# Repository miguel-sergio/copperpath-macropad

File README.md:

# RP2040 Macropad

A 9-key macropad with a rotary encoder and RGB lighting under every key, built around the RP2040.

I made it as an open project, so anyone can learn from it, change it or build one. The repo has the full KiCad project, the files to order it assembled at JLCPCB, and the notes behind the main design decisions.

## Features

- RP2040 with 2 MB QSPI flash (W25Q16JV)
- 9 MX hot-swap keys (change switches without soldering)
- EC11 rotary encoder with push button
- One SK6812MINI-E RGB LED under every key
- USB-C (USB 2.0 Full Speed) with ESD protection and a 500 mA polyfuse
- BOOT and RESET buttons to load firmware over USB
- SWD connector with the Raspberry Pi Debug Probe pinout
- 2-layer board, 87 × 68 mm, every SMD part on the bottom side
- BOM and placement files with LCSC part numbers, ready for JLCPCB assembly

## Design notes

### RGB LEDs through a 74AHCT1G125 buffer

The SK6812MINI-E LEDs run at 5 V, and they need at least 0.7 × VDD (3.5 V) to read a logic 1. The RP2040 gives only 3.3 V. Driving them directly "works" on most boards, but it is out of spec, and it can fail with a different LED batch, a longer chain or a lower temperature.

The 74AHCT1G125 runs at 5 V and accepts 3.3 V logic at its input, so it turns the 3.3 V data line into a clean 5 V signal. A 330 Ω resistor in series protects the first LED input.

The LEDs are reverse mount: they sit on the bottom side and shine up through a cutout in the PCB, into the LED window of the switch. The chain goes in a zigzag (right to left, left to right, right to left) to keep the data line short.

### Every SMD part on one side

The hot-swap sockets and the reverse mount LEDs must be on the bottom side, so I put all the other SMD parts there too. JLCPCB assembles the board in a single pass, which is cheaper than two-sided assembly. The top side only has the switches (they click into the sockets, no soldering) and the encoder, which is the only part you solder by hand.

Both copper layers have a ground pour. The top one is almost unbroken, because most signals run on the bottom.

### USB-C input

- 5.1 kΩ resistors on CC1 and CC2, so any USB-C port or charger gives 5 V
- USBLC6-2SC6 ESD protection close to the connector
- 27 Ω series resistors on D+ and D- next to the RP2040
- 500 mA polyfuse on VBUS

### Power

- AMS1117-3.3 LDO for the 3.3 V rail (a JLCPCB basic part, so no extra assembly fee)
- The RP2040 makes its 1.1 V core supply with its internal regulator
- The LEDs run from 5 V, with a 22 µF capacitor next to the first LED for the current peaks
- Keep the LED brightness limited in firmware, so the board stays inside the USB power budget

### Clock, flash and boot

- 12 MHz crystal (20 pF load) with 33 pF capacitors and a 1 kΩ resistor on XOUT, following the Raspberry Pi hardware design guide
- W25Q16JV flash in a small USON-8 package
- BOOT button on QSPI_SS (through 1 kΩ) and RESET button on RUN (with a 10 kΩ pull-up)

### Debug and test

- SWD on a 3-pin JST-SH connector (SWCLK, GND, SWDIO), the same as the Raspberry Pi Debug Probe cable
- Test points for GND, 5 V, 3.3 V, 1.1 V and the LED data line

### Mechanics

- Standard 19.05 mm key pitch, so any MX plate, keycap or case design fits
- Four M2 mounting holes, plated and connected to ground

## Pinout (for firmware)

| Function | RP2040 pin |
|---|---|
| KEY1 to KEY9 (SW3 to SW11) | GPIO0 to GPIO8 |
| Encoder signal A | GPIO9 |
| Encoder signal B | GPIO10 |
| Encoder push button | GPIO11 |
| LED data (through the 74AHCT1G125) | GPIO12 |
| SWD | SWCLK, SWDIO |

The encoder has two signals, A and B. Their order tells the firmware which way you turn the knob. Keys, the encoder and its button connect to ground, so use the internal pull-ups.

Key and LED position (top view). KEYx is the net name in the schematic, SWx and Dx are the reference designators on the board. D1 is the first LED in the chain, D9 the last.

| | Column 1 | Column 2 | Column 3 | Column 4 |
|---|---|---|---|---|
| **Row 1** | KEY1 (SW3) · D3 | KEY2 (SW4) · D2 | KEY3 (SW5) · D1 | USB-C |
| **Row 2** | KEY4 (SW6) · D4 | KEY5 (SW7) · D5 | KEY6 (SW8) · D6 | Encoder (ENC1) |
| **Row 3** | KEY7 (SW9) · D9 | KEY8 (SW10) · D8 | KEY9 (SW11) · D7 | |

SW1 and SW2 are the BOOT and RESET buttons, so the keys start at SW3.

## What is in this repo

| Path | Content |
|---|---|
| `macropad.kicad_pro`, `.kicad_sch`, `.kicad_pcb` | KiCad 10 project |
| `macropad.pdf` | Schematic in PDF |
| `macropad.kicad_dru` | Extra design rules for JLCPCB |
| `parts/` | Project library (hot-swap socket footprint and 3D models) |
| `production/` | Gerbers (`macropad.zip`), `bom.csv` and `positions.csv` for JLCPCB |
| `images/` | 3D renders |

## Ordering at JLCPCB

1. Upload `production/macropad.zip`. 2 layers, 1.6 mm, any color.
2. Turn on PCB Assembly and choose the **bottom** side.
3. Upload `production/bom.csv` and `production/positions.csv`.
4. Check the placement preview carefully: pin 1 of the RP2040, the LEDs, the USB-C connector, the SOT-23 parts and the hot-swap sockets (each one must sit over its two pads).
5. Solder the EC11 encoder by hand. It is not in the BOM.

## What else you need

- 9 MX switches (5-pin switches are best, they hold to the PCB without a plate)
- 9 MX keycaps and a knob for the encoder
- 4 M2 screws and standoffs, or a 3D printed case
- A USB-C cable with data lines (some cables only charge)

## Firmware

Firmware is not in this repo yet. The RP2040 is supported by QMK, KMK and the Pico SDK, and the pinout above is all you need. To load firmware, hold BOOT while you plug the USB cable (or press RESET), and the board shows up as a USB drive.

## License

This hardware is released under the [CERN Open Hardware Licence Version 2, Strongly Reciprocal](https://ohwr.org/cern_ohl_s_v2.txt) (CERN-OHL-S-2.0). See `LICENSE`.

## About

Designed by Miguel Sergio García ([Copperpath PCB](https://copperpathpcb.com)). I design and review PCBs for small companies and startups, mostly in KiCad and EasyEDA and ready for JLCPCB.

If you build one, change it or would do something different on this board, open an issue or tell me. I like to hear it.

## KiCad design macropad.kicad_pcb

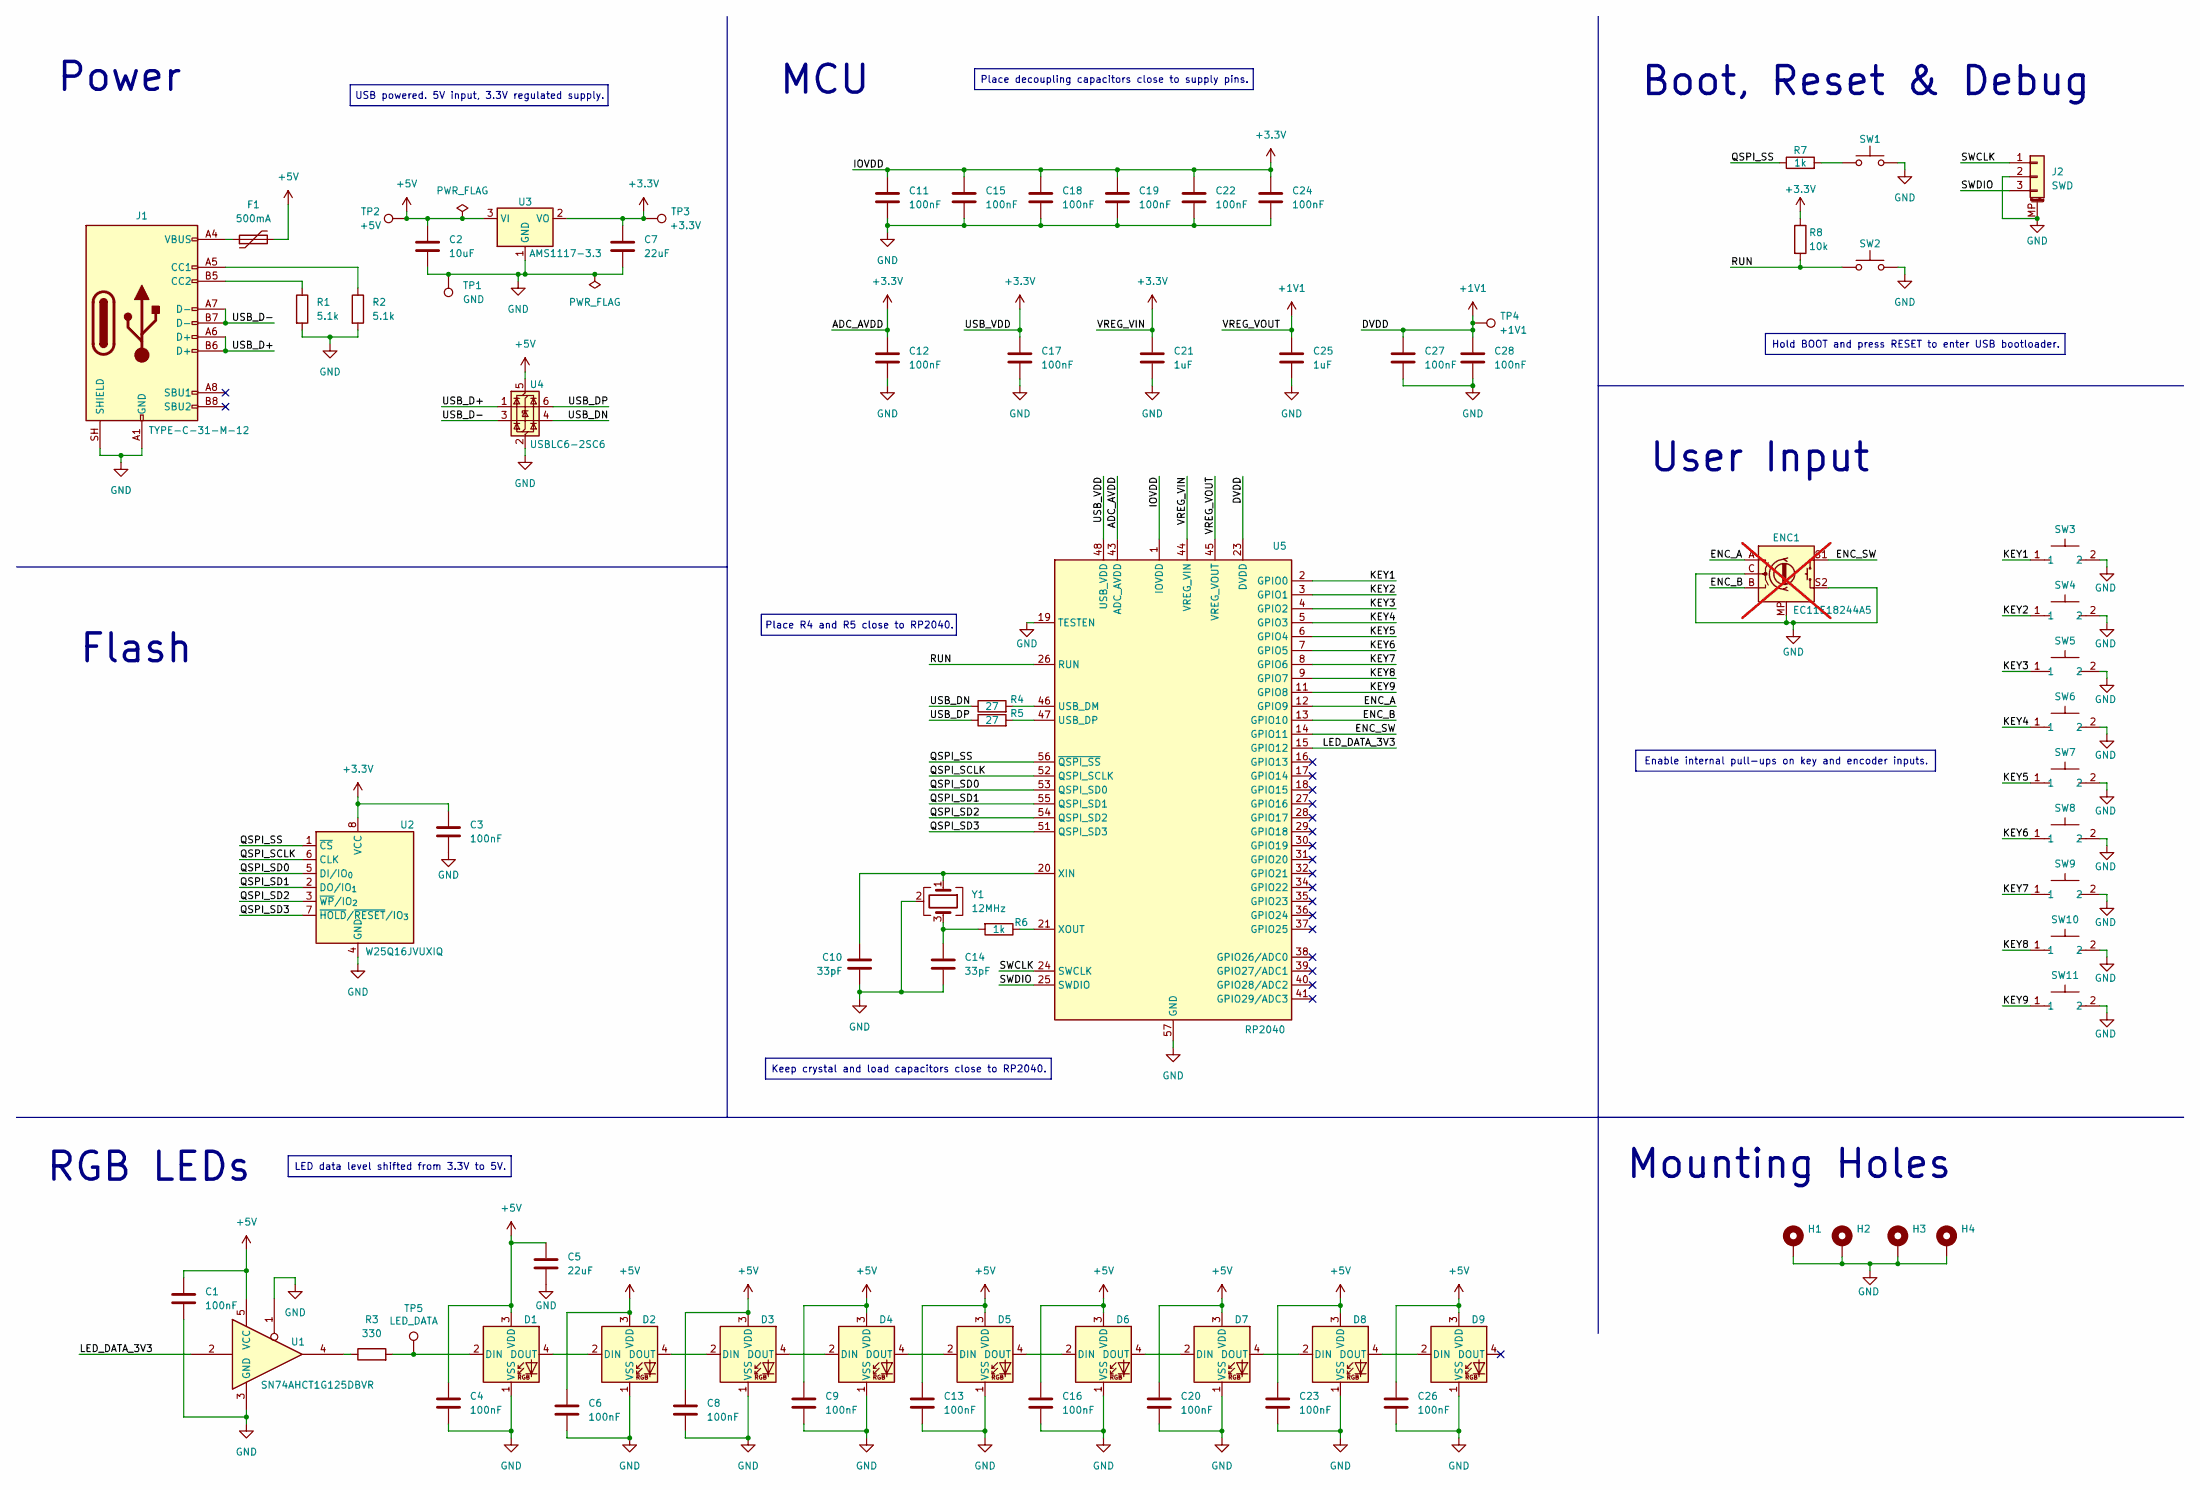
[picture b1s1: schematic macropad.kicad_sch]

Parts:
C1, C3, C4, C6, C8, C9, C11, C12, C13, C15, C16, C17, C18, C19, C20, C22, C23, C24, C26, C27, C28: 100nF; C_0402_1005Metric; LCSC Part # C1525
C2: 10uF; C_0603_1608Metric; LCSC Part # C19702
C5, C7: 22uF; C_0805_2012Metric; LCSC Part # C45783
C10, C14: 33pF; C_0402_1005Metric; LCSC Part # C1562
C21, C25: 1uF; C_0402_1005Metric; LCSC Part # C52923
D1, D2, D3, D4, D5, D6, D7, D8, D9: SK6812MINI-E; LED_SK6812MINI-E_3.2x2.8mm_P1.5mm_ReverseMount; LCSC Part # C5149201
ENC1: EC11E18244A5; RotaryEncoder_Alps_EC11E-Switch_Vertical_H20mm; LCSC Part # C255515; not fitted
F1: 500mA; Fuse_0805_2012Metric; LCSC Part # C883109
H1, H2, H3, H4: MountingHole_Pad; MountingHole_2.2mm_M2_Pad_Via
J1: TYPE-C-31-M-12; USB_C_Receptacle_HRO_TYPE-C-31-M-12; LCSC Part # C165948
J2: SWD; JST_SH_BM03B-SRSS-TB_1x03-1MP_P1.00mm_Vertical; LCSC Part # C160389
R1, R2: 5.1k; R_0402_1005Metric; LCSC Part # C25905
R3: 330; R_0402_1005Metric; LCSC Part # C25104
R4, R5: 27; R_0402_1005Metric; LCSC Part # C25100
R6, R7: 1k; R_0402_1005Metric; LCSC Part # C11702
R8: 10k; R_0402_1005Metric; LCSC Part # C25744
SW1: BOOTSEL; SW_Push_1P1T_XKB_TS-1187A; LCSC Part # C318884
SW2: RESET; SW_Push_1P1T_XKB_TS-1187A; LCSC Part # C318884
SW3, SW4, SW5, SW6, SW7, SW8, SW9, SW10, SW11: CPG151101S11-16; SW_Hotswap_Kailh_MX_1.00u; LCSC Part # C41430893
TP1: GND; TestPoint_Pad_D2.0mm
TP2: +5V; TestPoint_Pad_D2.0mm
TP3: +3.3V; TestPoint_Pad_D2.0mm
TP4: +1V1; TestPoint_Pad_D2.0mm
TP5: LED_DATA; TestPoint_Pad_D2.0mm
U1: SN74AHCT1G125DBVR; SOT-23-5; LCSC Part # C7484
U2: W25Q16JVUXIQ; Winbond_USON-8-1EP_3x2mm_P0.5mm_EP0.2x1.6mm; LCSC Part # C2843335
U3: AMS1117-3.3; SOT-223-3_TabPin2; LCSC Part # C6186
U4: USBLC6-2SC6; SOT-23-6; LCSC Part # C7519
U5: RP2040; QFN-56-1EP_7x7mm_P0.4mm_EP3.2x3.2mm; LCSC Part # C2040
Y1: 12MHz; Crystal_SMD_3225-4Pin_3.2x2.5mm; LCSC Part # C9002

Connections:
+1V1: C25.1, C27.1, C28.1, TP4.1 (1_1), U5.23 (DVDD), U5.45 (VREG_VOUT), U5.50 (DVDD)
+3.3V: C3.1, C7.1, C11.1, C12.1, C15.1, C17.1, C18.1, C19.1, C21.1, C22.1, C24.1, R8.1, TP3.1 (1_1), U2.8 (VCC), U3.2 (VO), U5.1 (IOVDD), U5.10 (IOVDD), U5.22 (IOVDD), U5.33 (IOVDD), U5.42 (IOVDD), U5.43 (ADC_AVDD), U5.44 (VREG_VIN), U5.48 (USB_VDD), U5.49 (IOVDD)
+5V: C1.1, C2.1, C4.1, C5.1, C6.1, C8.1, C9.1, C13.1, C16.1, C20.1, C23.1, C26.1, D1.3 (VDD), D2.3 (VDD), D3.3 (VDD), D4.3 (VDD), D5.3 (VDD), D6.3 (VDD), D7.3 (VDD), D8.3 (VDD), D9.3 (VDD), F1.2, TP2.1 (1_1), U1.5 (VCC), U3.3 (VI), U4.5 (VBUS)
/ENC_A: ENC1.A, U5.12 (GPIO9)
/ENC_B: ENC1.B, U5.13 (GPIO10)
/ENC_SW: ENC1.S1, U5.14 (GPIO11)
/KEY1: SW3.1, U5.2 (GPIO0)
/KEY2: SW4.1, U5.3 (GPIO1)
/KEY3: SW5.1, U5.4 (GPIO2)
/KEY4: SW6.1, U5.5 (GPIO3)
/KEY5: SW7.1, U5.6 (GPIO4)
/KEY6: SW8.1, U5.7 (GPIO5)
/KEY7: SW9.1, U5.8 (GPIO6)
/KEY8: SW10.1, U5.9 (GPIO7)
/KEY9: SW11.1, U5.11 (GPIO8)
/LED_DATA_3V3: U1.2, U5.15 (GPIO12)
/QSPI_SCLK: U2.6 (CLK), U5.52 (QSPI_SCLK)
/QSPI_SD0: U2.5 (DI/IO_{0}), U5.53 (QSPI_SD0)
/QSPI_SD1: U2.2 (DO/IO_{1}), U5.55 (QSPI_SD1)
/QSPI_SD2: U2.3 (~WP/IO_{2}), U5.54 (QSPI_SD2)
/QSPI_SD3: U2.7 (~HOLD/~RESET/IO_{3}), U5.51 (QSPI_SD3)
/QSPI_SS: R7.1, U2.1 (~CS), U5.56 (~QSPI_SS)
/RUN: R8.2, SW2.1, U5.26 (RUN)
/SWCLK: J2.1, U5.24 (SWCLK)
/SWDIO: J2.3, U5.25 (SWDIO)
/USB_D+: J1.A6 (D+), J1.B6 (D+), U4.1 (I/O1)
/USB_D-: J1.A7 (D-), J1.B7 (D-), U4.3 (I/O2)
/USB_DN: R4.1, U4.4 (I/O2)
/USB_DP: R5.1, U4.6 (I/O1)
GND: C1.2, C2.2, C3.2, C4.2, C5.2, C6.2, C7.2, C8.2, C9.2, C10.1, C11.2, C12.2, C13.2, C14.2, C15.2, C16.2, C17.2, C18.2, C19.2, C20.2, C21.2, C22.2, C23.2, C24.2, C25.2, C26.2, C27.2, C28.2, D1.1 (VSS), D2.1 (VSS), D3.1 (VSS), D4.1 (VSS), D5.1 (VSS), D6.1 (VSS), D7.1 (VSS), D8.1 (VSS), D9.1 (VSS), ENC1.C, ENC1.MP, ENC1.S2, H1.1 (1_1), H2.1 (1_1), H3.1 (1_1), H4.1 (1_1), J1.A1 (GND), J1.A12 (GND), J1.B1 (GND), J1.B12 (GND), J1.SH (SHIELD), J2.2, J2.MP (MountPin), R1.2, R2.2, SW1.2, SW2.2, SW3.2, SW4.2, SW5.2, SW6.2, SW7.2, SW8.2, SW9.2, SW10.2, SW11.2, TP1.1 (1_1), U1.1, U1.3 (GND), U2.4 (GND), U3.1 (GND), U4.2 (GND), U5.19 (TESTEN), U5.57 (GND), Y1.2 (G), Y1.4 (G)
unnamed: C14.1, R6.2, Y1.3
unnamed: D1.2 (DIN), R3.2, TP5.1 (1_1)
unnamed: D1.4 (DOUT), D2.2 (DIN)
unnamed: D2.4 (DOUT), D3.2 (DIN)
unnamed: D3.4 (DOUT), D4.2 (DIN)
unnamed: D4.4 (DOUT), D5.2 (DIN)
unnamed: D5.4 (DOUT), D6.2 (DIN)
unnamed: D6.4 (DOUT), D7.2 (DIN)
unnamed: D7.4 (DOUT), D8.2 (DIN)
unnamed: D8.4 (DOUT), D9.2 (DIN)
unnamed: F1.1, J1.A4 (VBUS), J1.A9 (VBUS), J1.B4 (VBUS), J1.B9 (VBUS)
unnamed: J1.A5 (CC1), R2.1
unnamed: J1.B5 (CC2), R1.1
unnamed: R3.1, U1.4
unnamed: R7.2, SW1.1
unnamed: R4.2, U5.46 (USB_DM)
unnamed: R5.2, U5.47 (USB_DP)
unnamed: C10.2, U5.20 (XIN), Y1.1
unnamed: R6.1, U5.21 (XOUT)

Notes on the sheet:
Place R4 and R5 close to RP2040.
Keep crystal and load capacitors close to RP2040.
Flash
LED data level shifted from 3.3V to 5V.
Power
Place decoupling capacitors close to supply pins.
Mounting Holes
RGB LEDs
MCU
Boot, Reset & Debug
Hold BOOT and press RESET to enter USB bootloader.
USB powered. 5V input, 3.3V regulated supply.
User Input
Enable internal pull-ups on key and encoder inputs.

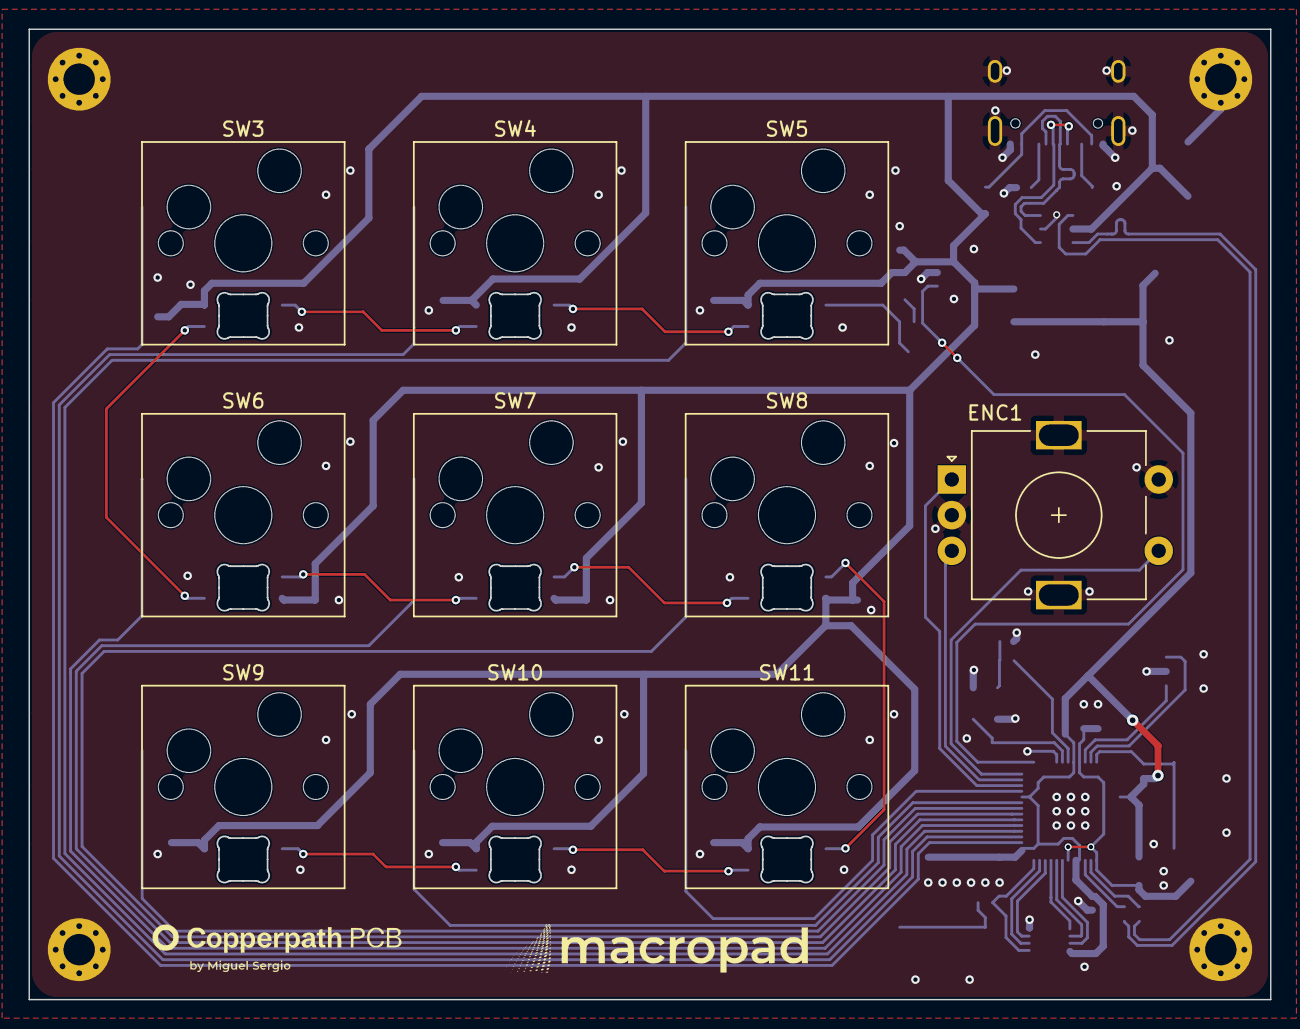
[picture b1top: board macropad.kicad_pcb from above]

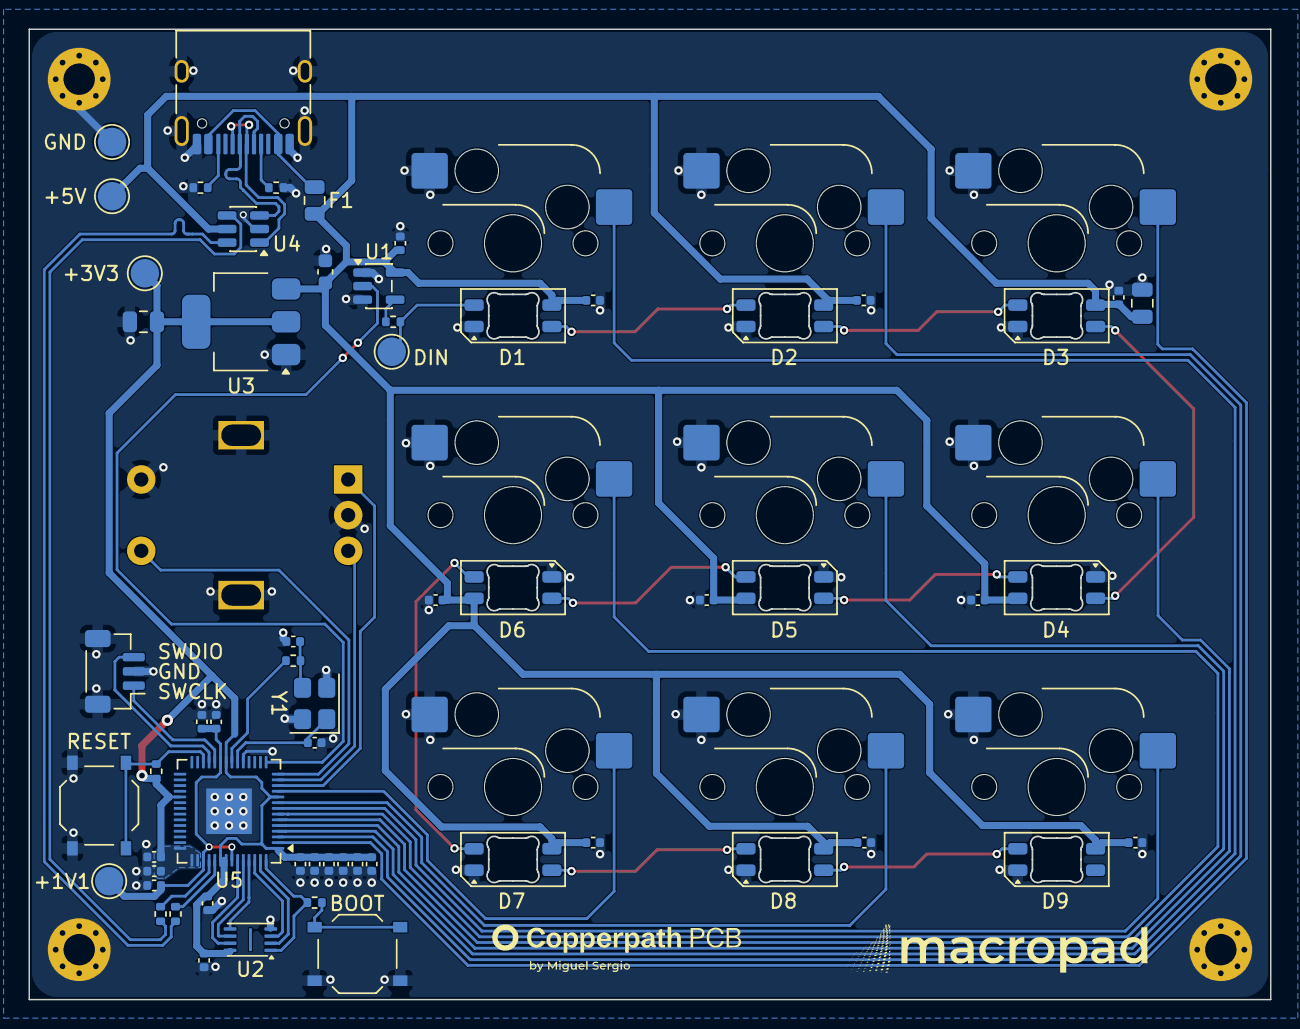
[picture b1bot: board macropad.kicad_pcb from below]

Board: 2 copper layers, 87.0 x 68.0 mm, 75 parts (61 on the bottom side), 49 nets.

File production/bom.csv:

Designator,Footprint,Quantity,Value,LCSC Part #
"C1, C11, C12, C13, C15, C16, C17, C18, C19, C20, C22, C23, C24, C26, C27, C28, C3, C4, C6, C8, C9",0402,21,100nF,C1525
"C10, C14",0402,2,33pF,C1562
C2,0603,1,10uF,C19702
"C21, C25",0402,2,1uF,C52923
"C5, C7",0805,2,22uF,C45783
"D1, D2, D3, D4, D5, D6, D7, D8, D9",LED_SK6812MINI-E_3.2x2.8mm_P1.5mm_ReverseMount,9,SK6812MINI-E,C5149201
F1,0805,1,500mA,C883109
J1,USB_C_Receptacle_HRO_TYPE-C-31-M-12,1,TYPE-C-31-M-12,C165948
J2,JST_SH_BM03B-SRSS-TB_1x03-1MP_P1.00mm_Vertical,1,SWD,C160389
"R1, R2",0402,2,5.1k,C25905
R3,0402,1,330,C25104
"R4, R5",0402,2,27,C25100
"R6, R7",0402,2,1k,C11702
R8,0402,1,10k,C25744
SW1,SW_Push_1P1T_XKB_TS-1187A,1,BOOTSEL,C318884
"SW10, SW11, SW3, SW4, SW5, SW6, SW7, SW8, SW9",SW_Hotswap_Kailh_MX_1.00u,9,CPG151101S11-16,C41430893
SW2,SW_Push_1P1T_XKB_TS-1187A,1,RESET,C318884
U1,SOT-23-5,1,SN74AHCT1G125DBVR,C7484
U2,Winbond_USON-8-1EP_3x2mm_P0.5mm_EP0.2x1.6mm,1,W25Q16JVUXIQ,C2843335
U3,SOT-223-3_TabPin2,1,AMS1117-3.3,C6186
U4,SOT-23-6,1,USBLC6-2SC6,C7519
U5,QFN-56-1EP_7x7mm_P0.4mm_EP3.2x3.2mm,1,RP2040,C2040
Y1,Crystal_SMD_3225-4Pin_3.2x2.5mm,1,12MHz,C9002

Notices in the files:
macropad.kicad_sch:
License: CERN-OHL-S-2.0
